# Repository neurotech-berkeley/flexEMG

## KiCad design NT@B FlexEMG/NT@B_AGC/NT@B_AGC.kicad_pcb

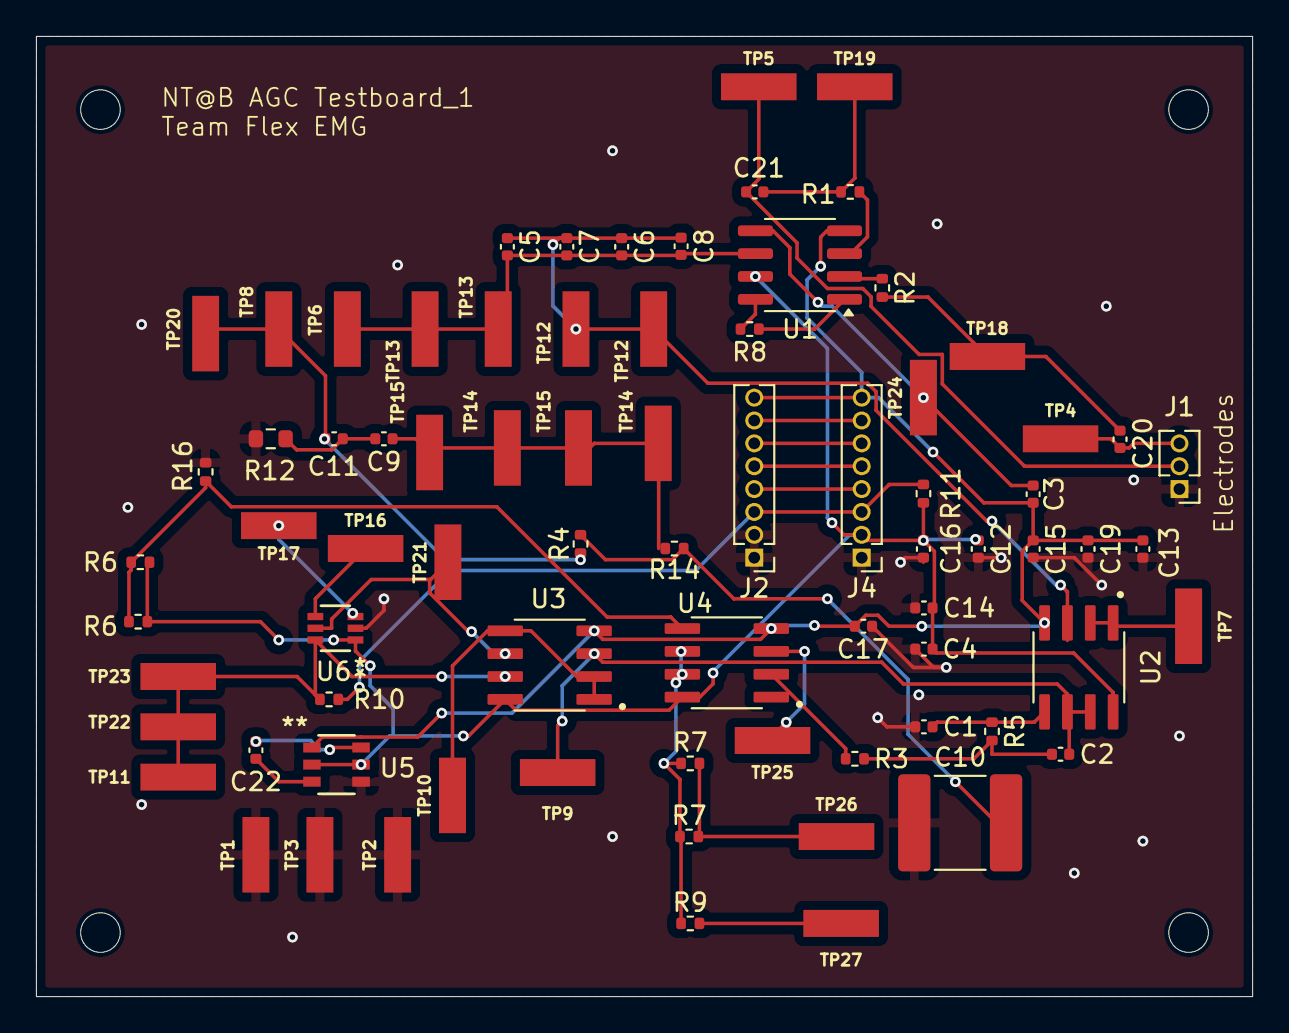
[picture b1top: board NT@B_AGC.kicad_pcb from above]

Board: 2 copper layers, 67.6 x 53.3 mm, 81 parts (0 on the bottom side), 35 nets.

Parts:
C1, C2, C5, C6, C7, C8, C20, C21: 10uF; C_0402_1005Metric
C3, C4, C12, C13, C14, C15, C16, C17: 0.1uF; C_0402_1005Metric
C9, C11, C19, C22: 1uF; C_0402_1005Metric
C10: 2uF; C_2220_5750Metric
H1, H1#2, H2, H3: MountingHole; MountingHole_2.2mm_M2
J1: Conn_01x03; PinHeader_1x03_P1.27mm_Vertical
J2, J4: Conn_01x08_Female; PinHeader_1x08_P1.27mm_Vertical
R1, R2: 220k; R_0402_1005Metric
R3, R5: 75R; R_0402_1005Metric
R4, R14: 2.7kΩ; R_0402_1005Metric
R6, R6#2, R16: 10kΩ; R_0402_1005Metric
R7, R7#2, R9: 100kΩ; R_0402_1005Metric
R8: 2k2; R_0402_1005Metric
R10, R11: 1k; R_0402_1005Metric
R12: 1.35kΩ; R_0603_1608Metric
TP1, TP2, TP7, TP8, TP9, TP10, TP11, TP12, TP12#2, TP13, TP13#2, TP14, TP14#2, TP15, TP15#2, TP16, TP17, TP18, TP19, TP20, TP21, TP22, TP23, TP24, TP25, TP26, TP27: TestPoint; TP420X150 (TestPointAGC)
TP3: 1 Raw; TP420X150 (TestPointAGC)
TP4: 3 Raw; TP420X150 (TestPointAGC)
TP5: 2 Raw; TP420X150 (TestPointAGC)
TP6: 1 & 2; TP420X150 (TestPointAGC)
U1: AD620; SOIC-8_3.9x4.9mm_P1.27mm
U2, U3, U4: LMC6492; LMC6492AEMXNOPB
U5: MAX1697REUT+T
U6: MCP4018T-104E/LT; MCP4018T-104ELT

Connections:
-VDD: C3.2, C13.2, C15.2, C17.2, C19.2, J2.8, J4.8, U1.4 (Vs-), U2.4 (V-), U3.4 (V-), U4.4 (V-), U5.1 (OUT)
/AMP_IN+_CH0: TP10.1, U3.1, U3.2 (-), U3.5 (+)
/AMP_OUT_CH0: R10.2, TP11.1, TP22.1, TP23.1, U3.7, U6.6 (A)
/HPF_OUT_CH0: C5.2, C6.2, C7.2, C8.2, TP12.1, TP12#2.1, U2.3 (+)
/IA_IN+_CH0: R1.2, U1.3 (+)
/IA_IN-_CH0: R2.2, U1.2 (-)
/IA_OUT_CH0: C5.1, C6.1, C7.1, C8.1, TP6.1, TP13.1, TP13#2.1, U1.6
/LPF_IN-_CH0: C2.2, TP9.1, U2.6 (-), U2.7, U3.3 (+)
AOUT_CH0: J2.3, J4.3, R10.1, R11.1
AOUT_CH1: J2.4, J4.4
AOUT_CH2: J2.5, J4.5
AOUT_CH3: J2.6, J4.6
AOUT_CH4: J2.7, J4.7
E1_CH0: C21.2, R1.1, TP19.1
E2_CH0: C20.2, R2.1, TP18.1
GND: C1.1, C4.1, C10.1, C12.1, C13.1, C14.1, C15.1, C16.1, C17.1, C19.1, J1.1, J2.1, J2.2, J4.1, R12.2, R16.2, TP1.1, TP2.1, TP3.1, U5.4 (GND), U6.2 (VSS)
I2C_SCL: TP17.1, U6.3 (SCL)
I2C_SDA: TP16.1, U6.4 (SDA)
NOTCH_OUT_CH0: TP25.1, U4.3 (+)
unnamed: C9.1, R14.2, TP14.1, TP14#2.1, TP15.1, TP15#2.1
unnamed: C10.2, R4.2, R14.1
unnamed: C20.1, J1.3, TP4.1
unnamed: C21.1, J1.2, TP5.1
unnamed: C11.2, R4.1, TP8.1, TP20.1
unnamed: R7.2, R7#2.2, TP26.1
unnamed: R9.2, TP27.1
unnamed: R6.2, R6#2.2, R16.1, U4.5 (+)
unnamed: R7.1, R7#2.1, R9.1, U4.6 (-), U4.7
unnamed: C22.2, U5.6 (C1+)
unnamed: C22.1, U5.3 (C1-)
unnamed: TP21.1, U3.6 (-), U6.5 (W)
SK00: R3.2, U4.1, U4.2 (-)
SK01: C2.1, R3.1, R5.2
SK11: C1.2, R5.1, U2.5 (+)
VDD: C4.2, C12.2, C14.2, C16.2, J4.2, R6.1, R6#2.1, R11.2, U1.7 (Vs+), U2.8 (V+), U3.8 (V+), U4.8 (V+), U5.2 (IN), U5.5 (~SHDN), U6.1 (VDD)

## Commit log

2024-10-26 Uploaded KiCAD FlexEMG PCB design files
    Folder contains completed schematic and layout files as well as backups
